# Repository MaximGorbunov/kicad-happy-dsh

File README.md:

# ⚡ kicad-happy

AI-powered design review for KiCad. Analyzes schematics, PCB layouts, and Gerbers. Catches real bugs before you order boards.

Built for **[DeepSeek Harness (DSH)](https://github.com/deepseek-ai/deepseek-harness)** — native skills for the desktop, web, TUI, and headless profiles — plus a **GitHub Action** for automated PR reviews, or standalone Python scripts you can run anywhere.

These skills turn your AI coding agent into a full-fledged electronics design assistant that understands your KiCad projects at a deep level: parses schematics and PCB layouts into structured data, cross-references component values against datasheets, detects common design errors, and walks you through the full prototype-to-production workflow.

## 🔬 What it looks like in practice

Point your agent at a KiCad project and it does the rest — parses every schematic and PCB file, traces every net, computes every voltage, and tells you what's wrong before you spend money on boards.

> "Analyze my KiCad project at `hardware/rev2/`"

Here's a condensed example from an open-source robot controller board. The agent found all of this automatically:

**It builds your power tree** — tracing every regulator from input to load, computing output voltages from feedback dividers:

```
VBUS (USB-C / battery input, fused)
├── AP63357 buck (500kHz switching) → 5V
│   └── Feedback: R8/R9 ratio=0.155 → Vout=3.87V
│       Power dissipation: ~0.15W (85% efficiency assumed)
└── RT9080-3.3 LDO → 3.3V
    └── Decoupling: 16 caps, 10.8µF total
```

**It identifies every subcircuit** — not just passives, but the functional blocks and how they connect:

| Subcircuit  | Details                                                                                       |
| ----------- | --------------------------------------------------------------------------------------------- |
| Motor drive | 9x P-MOSFET switches (DMG2305UX), transistor-driven H-bridges                                |
| Filters     | RC signal conditioning at 16Hz, 169Hz, and 1.03kHz (input filtering and debounce)             |
| Lighting    | WS2812B addressable LED chain on GPIO, 60mA estimated draw                                    |
| Sensors     | Onboard sensor interface, crystal oscillator with load cap validation                         |
| Protection  | ESD clamp on USB D+/D-, dual input fuses (0.75A signal, 2.5A motor)                          |

**It audits every connector for ESD protection** — and flags the ones that are exposed:

```
ESD coverage: 19 connectors audited

  USB-C:     ESD clamp on D+/D-  ✓ (partial — 13 signal pins per ground ⚠️)
  Fuse F1:   2.5A motor input  ✓
  Fuse F2:   0.75A signal input  ✓
  ⚠️ 6-pin header:    no protection (exposed signals)
  ⚠️ Motor outputs:   no protection (exposed to back-EMF)
  ⚠️ Servo connectors: no protection (exposed signals)
  ⚠️ Sensor port:     no protection
  ... 19 of 19 connectors have coverage gaps
```

**It validates your passive networks** — computing actual circuit behavior from component values:

| Detection | Components | Computed Value | What It Means |
|-----------|-----------|---------------|---------------|
| RC filter | R21/C31   | fc = 15.9 Hz  | Low-pass for slow analog signal |
| RC filter | R1/C13    | fc = 169 Hz   | Debounce / noise rejection |
| RC filter | R2/C14    | fc = 1.03 kHz | Signal conditioning |
| Feedback  | R8/R9     | ratio = 0.155 | Buck converter output voltage set |
| Divider   | R42/R43   | ratio = 0.500 | Voltage sensing (half) |
| Crystal   | Y1        | CL = 14.0 pF  | Load cap status: ok (target: 18 pF, -22%) |

**It suggests applicable certifications** — based on what it detects in the design:

```
Suggested certifications:
  FCC Part 15 Subpart B (US) — unintentional radiator compliance
  CISPR 32 / CE EMC Directive (EU) — EMC compliance for EU market
```

**It checks production readiness** — BOM lock status, connector ground distribution, decoupling adequacy:

```
BOM lock: 0% — no MPNs assigned (prototype stage)
Decoupling: 5 rails, 34 caps total (132µF motor, 110µF logic, 10.8µF 3.3V)
Connector ground: USB-C has 13:1 signal-to-ground ratio (recommended ≤3:1)
```

For complete examples with all sections, see:
- [Example 1: Robot controller](example-report-1.md) — schematic + PCB + EMC + SPICE, 184 components
- [Example 2: GNSS disciplined oscillator](example-report-2.md) — full workflow including datasheet sync, 296 components, 10 power rails, Ethernet + USB + SMA

For the end-to-end walkthrough from S-expression parsing through signal detection and datasheet cross-referencing, see [How It Works](how-it-works.md).

## 🚀 Install

> [!TIP]
> For detailed installation, upgrade, and troubleshooting guidance in DeepSeek
> Harness, have your AI agent read [`install-guidance.md`](install-guidance.md).
> It covers skill-discovery troubleshooting, Python version issues, and
> sandbox/approval behavior.

kicad-happy is a **DSH-native skill suite**. DSH discovers skills from a
project's `.dsh/skills/` directory (its highest-priority project root), which
this repo ships as a link to `skills/` — so cloning the repo is the install.

**Mode A — workspace install (recommended):**

```bash
git clone git@github.com:MaximGorbunov/kicad-happy-dsh.git
cd kicad-happy-dsh
```

Then open that directory as a workspace in DeepSeek Harness (desktop, web,
TUI, or headless) and start a session. All 12 skills — the `kicad-happy` hub
plus 11 domain skills — appear in the session's skill catalog automatically.
Try: *"Analyze my KiCad project at `hardware/rev2/`"*.

**Mode B — global install (every workspace):**

```bash
cd <path-to-this-repo>
./install.sh                 # macOS & Linux; idempotent
# ./install.sh --uninstall   # remove the global links again
```

`~/.dsh/skills/` is DSH's user-global skill root; the skills then load in
every workspace, not just this repo's. (The installer symlinks each skill
directory; DSH reads each skill's `SKILL.md` frontmatter for its name, so
the link targets are the skill directories themselves.)

**Mode C — pinned profile config (advanced):**

Prefer an explicit, machine-pinned path instead of symlinks? Add a
`skill-filesystem` config override to your DSH profile patch
(`~/.dsh/profiles/desktop/cordis.patch.yml` for the desktop profile):

```yaml
- id: skill-filesystem
  name: '@deepseek-ai/dsh-skill-filesystem'
  config:
    customSkillDirs:
      - /absolute/path/to/kicad-happy-dsh/skills
```

Custom skill dirs rank between project roots and user roots, so they coexist
with Modes A/B without name collisions (project-level skills win on a clash).

**Optional — MCP server (tool-level access from any workspace):**

The repo ships [`mcp/server.py`](mcp/README.md), a stdio MCP server exposing
the analyzers, BOM tools, and LCSC search as MCP tools. Wire it into a DSH
profile patch (`~/.dsh/profiles/<profile>/cordis.patch.yml`):

```yaml
- insert:
    - id: mcp-kicad-happy
      name: '@deepseek-ai/dsh-mcp-client'
      config:
        serverName: kicad-happy
        transport: stdio
        command: python3 /absolute/path/to/kicad-happy-dsh/mcp/server.py
```

See [mcp/README.md](mcp/README.md) for the tool list and options.

The analysis scripts are **pure Python 3.10+** with zero required
dependencies. No pip install, no Docker, no KiCad installation needed. DSH
bundles Python 3.12, so no separate Python setup is required even on macOS
(where the system `python3` is 3.9 — below this suite's minimum).

### Release candidates

Clone the repo and check out the RC tag, then use Mode A or B as above:

```bash
git clone git@github.com:MaximGorbunov/kicad-happy-dsh.git
cd kicad-happy-dsh
git checkout vX.Y.Z-rc.N
```

> [!IMPORTANT]
> Release candidates are pre-release builds intended for evaluation and
> feedback. They have passed the corpus regression gate and contract test
> suite but haven't completed extended manual validation. File issues on
> GitHub if you hit problems.

## ⚙️ GitHub Action

Also available as a **GitHub Action** for automated PR reviews. Every push and PR that touches KiCad files gets a commit status check and a structured review comment — power tree, SPICE results, EMC risk, thermal analysis, and more. For AI-driven reviews inside DeepSeek Harness (e.g. on a self-hosted runner), see the `dsh headless` example in [github-action.md](github-action.md).

See the **[GitHub Action setup guide](github-action.md)** for workflow examples, diff-based PR reviews, and AI-powered review configuration.

## 📦 Skills

| Skill         | What it does                                                                                                                                                                             |
| ------------- | ---------------------------------------------------------------------------------------------------------------------------------------------------------------------------------------- |
| **kicad-happy** | 🧭 Hub — orchestrates the full suite for complete reviews and multi-board/multi-MPN work (parallel subagents, workflows, report delivery).                                    |
| **kicad**     | ⚡ Parse and analyze KiCad schematics, PCB layouts, Gerbers, and PDF reference designs. Automated subcircuit detection, design review, DFM.                                               |
| **spice**     | 🔬 SPICE simulation — generates testbenches for detected subcircuits, validates filter frequencies, opamp gains, divider ratios. Monte Carlo tolerance analysis. ngspice, LTspice, Xyce. |
| **emc**       | 📡 EMC pre-compliance — 44 rule checks for radiated emission risks, PDN impedance, diff pair skew, ESD paths. FCC/CISPR/automotive/military.                                             |
| **datasheets**| 📄 Extract structured specs from datasheet PDFs — pinouts, electrical characteristics, peripherals, topology. Per-MPN caching with quality scoring. Consumed by kicad/emc/spice/thermal. |
| **bom**       | 📋 Full BOM lifecycle — analyze, source, price, export tracking CSVs, generate per-supplier order files.                                                                                 |
| **digikey**   | 🔎 Search DigiKey for components and download datasheets via API.                                                                                                                        |
| **mouser**    | 🔎 Search Mouser for components and download datasheets.                                                                                                                                 |
| **lcsc**      | 🔎 Search LCSC for components (production sourcing, JLCPCB parts library).                                                                                                               |
| **element14** | 🔎 Search Newark/Farnell/element14 (one API, three storefronts).                                                                                                                         |
| **jlcpcb**    | 🏭 JLCPCB fabrication and assembly — design rules, BOM/CPL format, ordering workflow.                                                                                                    |
| **pcbway**    | 🏭 PCBWay fabrication and assembly — turnkey with MPN-based sourcing.                                                                                                                    |

## 🖐️ Ask about specific circuits

You don't have to ask for a full design review — just point the agent at whatever you're working on:

> "Check the two capacitive touch buttons on my PCB for routing or placement issues"

> "Is my boost converter loop area going to cause EMI problems?"

> "Trace the enable chain for my power sequencing — is the order correct?"

> "Are the differential pairs on my USB routed correctly?"

The agent runs the analysis scripts, then autonomously digs deeper — tracing nets, analyzing zone fills, calculating clearances, reading datasheets.

## What the analysis covers

| Domain            | What it checks                                                                                                                                                                                                 |
| ----------------- | -------------------------------------------------------------------------------------------------------------------------------------------------------------------------------------------------------------- |
| **Power**         | Regulator Vout from feedback dividers (~65 Vref families), power sequencing, enable chains, inrush, sleep current                                                                                              |
| **Analog**        | Opamp gain/bandwidth (per-part behavioral models), voltage dividers, RC/LC filters, crystal load caps                                                                                                          |
| **Protection**    | TVS/ESD mapping, reverse polarity FETs, fuse sizing, clamping voltage                                                                                                                                          |
| **Digital**       | I2C pull-up validation with rise time calculation, SPI CS counts, UART voltage domains, CAN termination                                                                                                        |
| **Domain**        | RF chains, Ethernet, HDMI, memory, BMS, motor drivers, sensors, display/touch, audio, LED drivers, debug interfaces, and more (40 detectors total)                                                             |
| **Derating**      | Capacitor voltage (ceramic 50%/electrolytic 80%), IC abs max, resistor power. Commercial/military/automotive profiles. Over-designed component detection.                                                      |
| **PCB**           | Thermal via adequacy, zone stitching, trace width vs current, DFM scoring, impedance, proximity/crosstalk                                                                                                      |
| **Manufacturing** | MPN coverage audit, JLCPCB/PCBWay format export, assembly complexity scoring                                                                                                                                   |
| **Lifecycle**     | Component EOL/NRND/obsolescence alerts, temperature grade audit, alternative part suggestions                                                                                                                  |
| **Thermal**       | Junction temperature estimation for LDOs, switching regulators, shunt resistors. Package Rθ_JA lookup, PCB thermal via correction, proximity warnings for caps near hotspots.                                  |
| **EMC**           | Ground plane voids, decoupling, I/O filtering, switching harmonics, clock routing, diff pair skew, board edge radiation, PDN impedance, ESD paths, crosstalk, thermal derating. FCC/CISPR/automotive/military. |

## 🔬 SPICE simulation

> "Sweep my LC matching network and show me where it actually resonates vs where I designed it"

> "What's the actual phase margin on my opamp filter stage with this TL072?"

> "Run SPICE on everything the analyzer detected and tell me what doesn't look right"

The **spice** skill goes beyond static analysis. It automatically generates SPICE testbenches for detected subcircuits — RC/LC filters, voltage dividers, opamp stages, feedback networks, transistor switches, crystal oscillators — runs them, and reports whether simulated behavior matches calculated values.

For recognized opamps (~100 parts), it uses **per-part behavioral models** with the real GBW, slew rate, and output swing from distributor APIs or a built-in lookup table. When both schematic and PCB exist, it injects **PCB trace parasitics** into the simulation.

```
Simulation: 14 pass, 1 warn, 0 fail
  RC filter R5/C3 (fc=15.9kHz): confirmed, <0.3% error
  Opamp U4A (inverting, gain=-10): 20.0dB confirmed
    Bandwidth 98.8kHz (LM324 behavioral, GBW=1.0MHz)
    Note: signal frequency should stay below 85kHz for <1dB gain error
```

**Monte Carlo tolerance analysis** — run N simulations per subcircuit with randomized component values within tolerance bands. Shows which component dominates output variation:

```
Monte Carlo (N=100): RC filter R5/C3
  fc: 15.9kHz ± 1.8kHz (3σ), spread 22.6%
  Sensitivity: C3 (10%) contributes 68%, R5 (5%) contributes 32%
```

**What-if parameter sweep** — instantly see the impact of component changes without editing the schematic:

```
> "What happens if I change R5 from 10k to 4.7k?"

  RC filter R5/C3: cutoff 1.59kHz → 3.39kHz (+112.8%)
  Voltage divider R5/R6: ratio 0.32 → 0.50 (+56.4%)
```

Requires ngspice, LTspice, or Xyce (auto-detected). Without one, simulation is skipped — the rest of the analysis still works. For the full methodology — see **[SPICE Integration Guide](spice-integration.md)**.

## 📡 EMC pre-compliance

> "Will my board pass FCC Class B? Check for EMC issues."

> "Analyze my switching regulator layout for EMI problems"

> "Check my differential pairs for skew-induced common-mode radiation"

The **emc** skill predicts the most common causes of EMC test failures — ground plane voids, insufficient decoupling, unfiltered I/O cables, switching regulator harmonics, differential pair skew, and more. It operates on the schematic and PCB analyzer output using geometric rule checks and analytical emission formulas (Ott, Paul, Bogatin). When ngspice is available, PDN impedance and EMI filter checks are SPICE-verified for higher accuracy — otherwise analytical models are used as fallback.

```
EMC risk score: 73/100
  CRITICAL: 1 — SPI_CLK crosses ground plane void on In1.Cu
  HIGH:     2 — USB diff pair 5.2mm skew (exceeds 25ps limit),
                no ground via near TVS U5
  MEDIUM:   3 — decoupling cap 7mm from U3, clock on outer layer,
                via stitching gap near J2
  INFO:     4 — cavity resonance at 715 MHz, switching harmonics
                in 30-88 MHz band

Pre-compliance test plan:
  Focus band: 30-88 MHz (12 switching harmonics from U1, U4)
  Highest risk interface: J1 (USB-C, unfiltered, 480 Mbps)
  Probe points: L1 (45.2, 32.1)mm, Y1 (62.0, 18.5)mm
```

44 rule checks across power integrity, signal integrity, and radiation. Includes full-board PDN impedance with power tree analysis — traces impedance from regulator output through PCB traces to IC load points, and detects cross-rail coupling when a downstream switching regulator injects transients onto the upstream rail. Supports FCC, CISPR, automotive (CISPR 25), and military (MIL-STD-461G) standards. Generates a pre-compliance test plan with frequency band priorities, interface risk rankings, and near-field probe points. For the full methodology — see **[EMC Pre-Compliance Guide](emc-precompliance.md)**.

## 📄 Datasheets — sync and extract

> "Sync datasheets for my board at `hardware/rev2/`"

> "What's the EN-pin threshold on the LDO I'm using?"

Datasheets flow through kicad-happy in two stages:

**Sync (download).** Pulls PDFs for every component with an MPN from DigiKey, LCSC, element14, or Mouser into a local `datasheets/` directory. 96% success rate across 240+ manufacturers. Each PDF is verified against the expected part number.

**Extract (parse).** The **datasheets** skill turns those PDFs into structured JSON — pinouts, voltage ratings, electrical characteristics, peripherals, topology, SPICE model coefficients. Extractions are cached per-MPN under `<project>/datasheets/extracted/` and scored on a five-dimension quality rubric. Analyzer skills (`kicad`, `emc`, `spice`, `thermal`) consume the cache through a shared helper API with trust gates — so a schematic finding tagged `confidence: datasheet-backed` means a scored extraction produced the underlying fact, not a keyword match on the part number.

For the full pipeline — page selection, the quality rubric, the consumer API, and what it deliberately doesn't do — see **[Datasheet Extraction Guide](datasheet-extraction.md)**.

## 📋 BOM management — from schematic to order

> "Source all the parts for my board, I'm building 5 prototypes"

The BOM skill manages the full lifecycle of your bill of materials — using your KiCad schematic as the single source of truth. No separate spreadsheets to keep in sync, no copy-pasting between tabs.

The agent analyzes your schematic to detect which distributor fields are populated (and which naming convention you're using — it handles dozens of variants like `Digi-Key_PN`, `DigiKey Part Number`, `DK`, etc.), identifies gaps, searches distributors to fill them, validates every match, and exports per-supplier order files in the exact upload format each distributor expects.

> "I need a 3.3V LDO that can do 500mA in SOT-223, under $1"

```
AZ1117CH-3.3TRG1 — Arizona Microdevices
  3.3V Fixed, 1A, SOT-223-3
  $0.45 @ qty 1, $0.32 @ qty 100
  In stock: 15,000+

AP2114H-3.3TRG1 — Diodes Incorporated
  3.3V Fixed, 1A, SOT-223
  $0.38 @ qty 1, $0.28 @ qty 100
  In stock: 42,000+
```

## 🏭 Manufacturing

> "Is this board ready to order?"

> "Generate the BOM for JLCPCB assembly"

**Fab release gate** — an automated pre-order checklist that cross-references your schematic, PCB, and Gerber data:

```
Fabrication Release Gate — 8 check categories

  Routing completeness     ✓ PASS  All 240 nets routed
  BOM readiness            ⚠ WARN  3 components missing MPN
  DFM compliance           ✓ PASS  No spacing violations, standard tier compatible
  Documentation            ✓ PASS  Title block, revision, fab notes present
  Schematic ↔ PCB match    ✓ PASS  296 components matched, 0 orphans
  Gerber verification      ✓ PASS  All layers present, drill file valid
  Thermal analysis         ⚠ WARN  U3 junction temp 92°C (margin: 18°C)
  EMC pre-compliance       ⚠ WARN  Score 73/100 — 2 HIGH findings

  Result: CONDITIONAL PASS (3 warnings to review before ordering)
```

**BOM export** — cross-references LCSC part numbers, formats to JLCPCB's exact spec, flags basic vs extended parts. Per-supplier upload files — DigiKey bulk-add CSV, Mouser cart format, LCSC BOM — with quantities already computed for your board count + spares.

## 🗺️ Workflow

1. **Design** your schematic and lay out the PCB in KiCad
2. **Sync datasheets** — the agent downloads PDFs and extracts structured specs for every MPN
3. **Design review** — the agent runs schematic, PCB, cross-analysis, EMC, SPICE, and thermal analyzers, cross-references against datasheets, and writes a structured report with findings ranked by severity
4. **Iterate** — fix issues, re-run the review, compare against the previous run with built-in diff analysis
5. **Source** components from DigiKey/Mouser (prototype) or LCSC (production)
6. **Export** BOM + per-supplier order files for your assembler
7. **Order** from JLCPCB or PCBWay with generated BOM/CPL files

Or set up the [GitHub Action](github-action.md) and get automated analysis on every PR.

## Optional setup

**SPICE simulator** (for the spice skill): `apt install ngspice` or LTspice or Xyce. Auto-detected.

**API keys** (for distributor skills — falls back to web search without them):

| Service   | Env variable                                 | Notes                                                   |
| --------- | -------------------------------------------- | ------------------------------------------------------- |
| DigiKey   | `DIGIKEY_CLIENT_ID`, `DIGIKEY_CLIENT_SECRET` | [developer.digikey.com](https://developer.digikey.com/) |
| Mouser    | `MOUSER_SEARCH_API_KEY`                      | My Mouser → APIs                                        |
| element14 | `ELEMENT14_API_KEY`                          | [partner.element14.com](https://partner.element14.com/) |
| LCSC      | *none*                                       | Free community API                                      |

**Optional Python packages**: `requests` (better HTTP), `playwright` (JS-heavy datasheet sites), `pdftotext` (PDF text extraction).

## ✅ KiCad version support

| Version  | Schematic                     | PCB  | Gerber |
| -------- | ----------------------------- | ---- | ------ |
| KiCad 10 | Full                          | Full | Full   |
| KiCad 9  | Full                          | Full | Full   |
| KiCad 8  | Full                          | Full | Full   |
| KiCad 7  | Full                          | Full | Full   |
| KiCad 6  | Full                          | Full | Full   |
| KiCad 5  | Full (legacy `.sch` + `.lib`) | Full | Full   |

## 🎯 Release notes

**Current release: v2.3.2 — backport.** AM-001 absolute-maximum checks resolve the `<domain>_max` keys real datasheet extractions carry; the datasheets scripts are UTF-8-safe on Windows; PU-001 skips no-connect pins, PP-001 skips gate-driver bootstrap pins, RS-001 reports heuristic confidence on rails it recognises only by name, and `cross_analysis.py` gives a usage error instead of a traceback on a bad input path. Upgrading: additive except the RS-001 confidence shift on name-only rails.

**Previous: v2.3.0 — correctness batch.** Eighteen verified fixes plus three community contributions: CP-003 touch-pad clearance is measured against real copper (it reported 0.0 mm on most boards and fired on test points), decoupling-distance findings only pair capacitors that actually share a supply net with the IC, the power budget and sleep-current audit stop dropping loads and rails, PD-001 no longer mistakes feedback feedforward caps for decouplers, and the datasheet-authority gates finally receive the project directory. New: **SP-001** catches a two-pin part wired to a single net (invisible to ERC), and `search_lcsc.py` searches the LCSC/JLCPCB catalog from the terminal. Datasheet sync no longer crashes on Windows when it re-saves its manifest. Upgrading: the EMC PD-001 field `transient_amps` is now `transient_a`; everything else is additive.

**Previous: v2.2.1 — maintenance batch.** Twenty-five verified fixes: the GP-001 via-antipad and power-rail-classification false positives from the field are gone, no-connect markers no longer absorb pins into wires passing beneath them (community-contributed, `kicad-cli`-verified), internal-oscillator IC descriptions stop triggering false clock findings, and a whole class of output nondeterminism was eliminated with a CI guard to keep it that way. Skipped or degraded analysis is now visible (`checks_run` manifest, connectivity-error notes, conditional-rule skip counts). Upgrading: GitHub Action users with multi-project repos must set the `schematic`/`pcb` inputs explicitly (auto-detect now fails loudly instead of guessing), and `analyze_pcb.py --schematic analysis/schematic.json` now classifies your declared power rails correctly.

Per-release stories are in [release-notes.md](release-notes.md); line-level detail in the [CHANGELOG](CHANGELOG.md).

## 🧪 Test harness

Everything above was validated against a [corpus of 5,800+ open-source KiCad projects](https://github.com/aklofas/kicad-happy-testharness) — the kind of designs real engineers actually build. The corpus spans hobby boards, production hardware, motor controllers, RF frontends, battery management systems, IoT devices, audio amplifiers, and everything in between. KiCad 5 through 10. Single-sheet and multi-sheet hierarchical. 2-layer through 6-layer. For full methodology and reproducibility instructions, see [VALIDATION.md](VALIDATION.md).

**The numbers:**

| Metric                       | Value                                        |
| ---------------------------- | -------------------------------------------- |
| Repos in corpus              | 5,800+                                       |
| Schematic files analyzed     | 6,845 (100% success)                         |
| PCB files analyzed           | 3,498 (99.9%)                                |
| Gerber directories analyzed  | 1,050 (100% success)                         |
| EMC pre-compliance analyses  | 6,853 (100% success, 141K+ findings)         |
| Components parsed            | 312,956                                      |
| Nets traced                  | 531,418                                      |
| SPICE subcircuit simulations | 30,646 across 17 types                       |
| SPICE-verified EMC findings  | 169 (PDN impedance via ngspice)              |
| Regression assertions        | 808K+ at 100% pass rate                      |
| Equations tracked & verified | 86 with source citations                     |
| Bugfix regression guards     | 67 (100% pass — no fixed bugs have returned) |
| Closed analyzer issues       | 193                                          |

Three-layer regression testing catches drift at every level:

| Layer          | What it catches                                                                                   |
| -------------- | ------------------------------------------------------------------------------------------------- |
| **Baselines**  | Output drift between analyzer versions                                                            |
| **Assertions** | Hard regressions on known-good results (component counts, detected subcircuits, signal paths)     |
| **LLM review** | Semantic issues deterministic checks miss — findings get promoted to machine-checkable assertions |

## 🎨 Why KiCad?

This project exists because **KiCad is absolutely incredible**. Fully open-source, cross-platform, backed by CERN, with a community that ships features faster than most commercial tools. It's used everywhere from weekend hobby projects to production hardware at real companies.

But what makes KiCad truly special for AI-assisted design — and the entire reason this project can exist — is its **beautifully open file format**. Every schematic, PCB layout, symbol, and footprint is stored as clean, human-readable S-expressions. No proprietary binary blobs. No vendor lock-in. No $500 "export plugin" just to read your own data.

This means your AI agent can read your KiCad files directly, understand every component, trace every net, and reason about your design at the same level a human engineer would. No KiCad export plugins, no export steps, no intermediary formats. Just your KiCad project and a terminal.

Try doing that with Altium or OrCAD. 😉

## 📜 License

MIT — see [CHANGELOG.md](CHANGELOG.md) for release history and [CONTRIBUTING.md](CONTRIBUTING.md) for development guidelines.

---

*Built for [DeepSeek Harness](https://github.com/deepseek-ai/deepseek-harness).* 🤖

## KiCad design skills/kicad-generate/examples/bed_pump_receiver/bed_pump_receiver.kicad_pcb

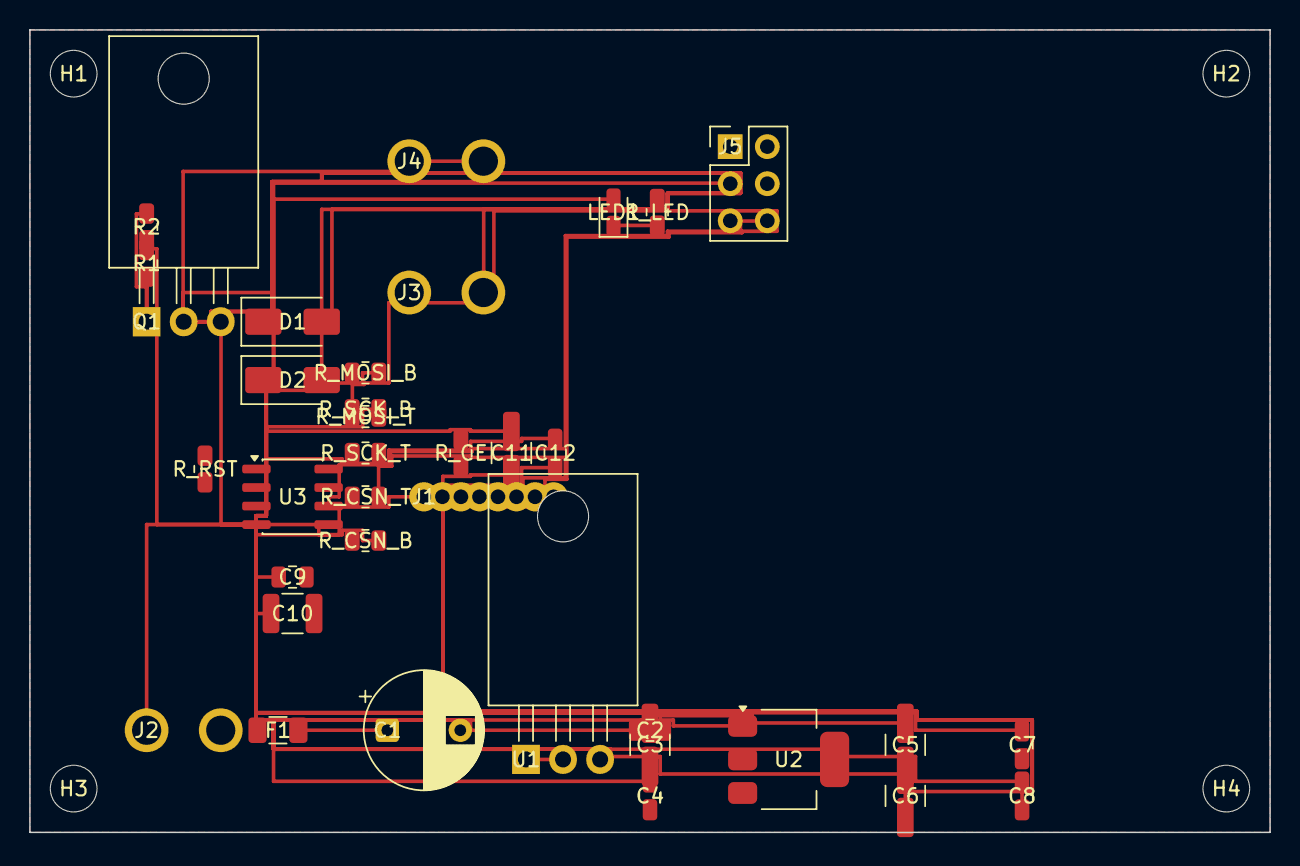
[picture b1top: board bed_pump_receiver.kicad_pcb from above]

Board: 2 copper layers, 85.0 x 55.0 mm, 40 parts (0 on the bottom side), 17 nets.

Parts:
C1: CP_Radial_D8.0mm_P5.00mm
C2, C4, C7, C8, C9, C12: C_0805_2012Metric
C3, C5, C6, C10, C11: C_1210_3225Metric
D1, D2: D_SMA
F1: Fuse_1206_3216Metric
H1, H2, H3, H4: MountingHole_3.2mm_M3
J1: nRF24L01P_Socket_8x1.27
J2, J3, J4: Screw_Terminal_01x02_P5.08
J5: PinHeader_2x03_P2.54mm_Vertical
LED1: LED_0805_2012Metric
Q1: TO-220-3_Horizontal_TabDown
R1, R2: R_0805_2012Metric
R_CE: R_0805_2012Metric
R_CSN_B: R_0805_2012Metric
R_CSN_T: R_0805_2012Metric
R_LED: R_0805_2012Metric
R_MOSI_B: R_0805_2012Metric
R_MOSI_T: R_0805_2012Metric
R_RST: R_0805_2012Metric
R_SCK_B: R_0805_2012Metric
R_SCK_T: R_0805_2012Metric
U1: TO-220-3_Horizontal_TabDown
U2: SOT-223-3_TabPin2
U3: SOIC-8_3.9x4.9mm_P1.27mm

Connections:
3V3: C6.2, C8.2, C11.2, C12.2, J1.2, R_CE.1, U2.2
5V: C3.2, C4.2, C5.2, C7.2, C9.2, C10.2, J5.1, R_LED.1, R_RST.1, U1.3, U2.3, U3.5
CE: J1.3, R_CE.2
CSN_D: J1.4, R_CSN_B.1, R_CSN_T.2
CSN_MCU: R_CSN_T.1, U3.2
GATE: Q1.1, R1.2, R2.1
GND: C1.1, C2.1, C3.1, C4.1, C5.1, C6.1, C7.1, C8.1, C9.1, C10.1, C11.1, C12.1, J1.1, J2.1, J5.2, LED1.1, Q1.3, R2.2, R_CSN_B.2, R_MOSI_B.2, R_SCK_B.2, U1.2, U2.1, U3.4
LED_A: LED1.2, R_LED.2
MISO: J1.7, J5.5, U3.7
MOSI_D: J1.6, R_MOSI_B.1, R_MOSI_T.2
MOSI_MCU: J5.4, R_MOSI_T.1, U3.8
PUMP: R1.1, U3.3
PUMP_D: D1.2, D2.2, J3.2, J4.2, Q1.2
RST: J5.3, R_RST.2, U3.1
SCK_D: J1.5, R_SCK_B.1, R_SCK_T.2
SCK_MCU: J5.6, R_SCK_T.1, U3.6
VBAT: C1.2, C2.2, D1.1, D2.1, F1.1, F1.2, J2.2, J3.1, J4.1, U1.1
